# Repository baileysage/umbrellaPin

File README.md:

# umbrellaPin
Umbrella PCB for soldering classes ages ~8-14

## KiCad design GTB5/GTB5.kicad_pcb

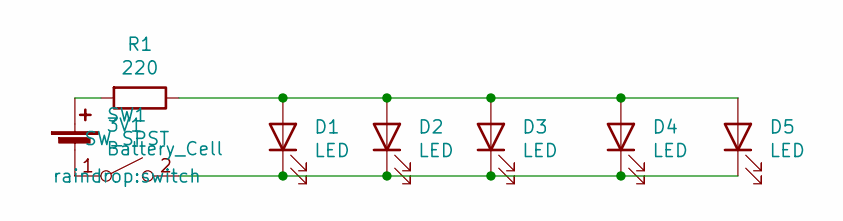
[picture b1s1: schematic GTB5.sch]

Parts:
3V1: Battery_Cell; BatteryHolder_BK_883
D1, D2, D3, D4, D5: LED; LED_D3.0mm_Clear
R1: 220; R_Axial_DIN0204_L3.6mm_D1.6mm_P7.62mm_Horizontal
SW1: SW_SPST; switch

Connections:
unnamed: 3V1.1 (+), R1.2
unnamed: 3V1.2 (-), SW1.1 (A)
unnamed: D1.1 (K), D2.1 (K), D3.1 (K), D4.1 (K), D5.1 (K), SW1.2 (B)
unnamed: D1.2 (A), D2.2 (A), D3.2 (A), D4.2 (A), D5.2 (A), R1.1

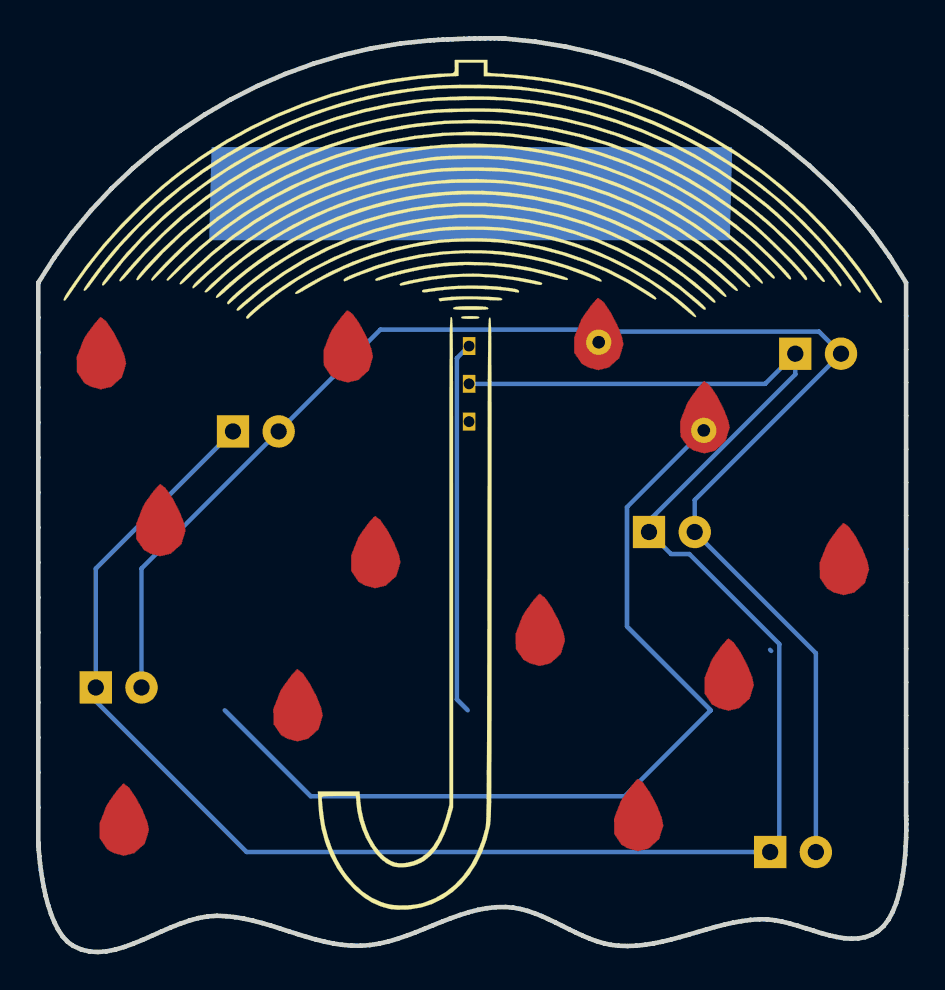
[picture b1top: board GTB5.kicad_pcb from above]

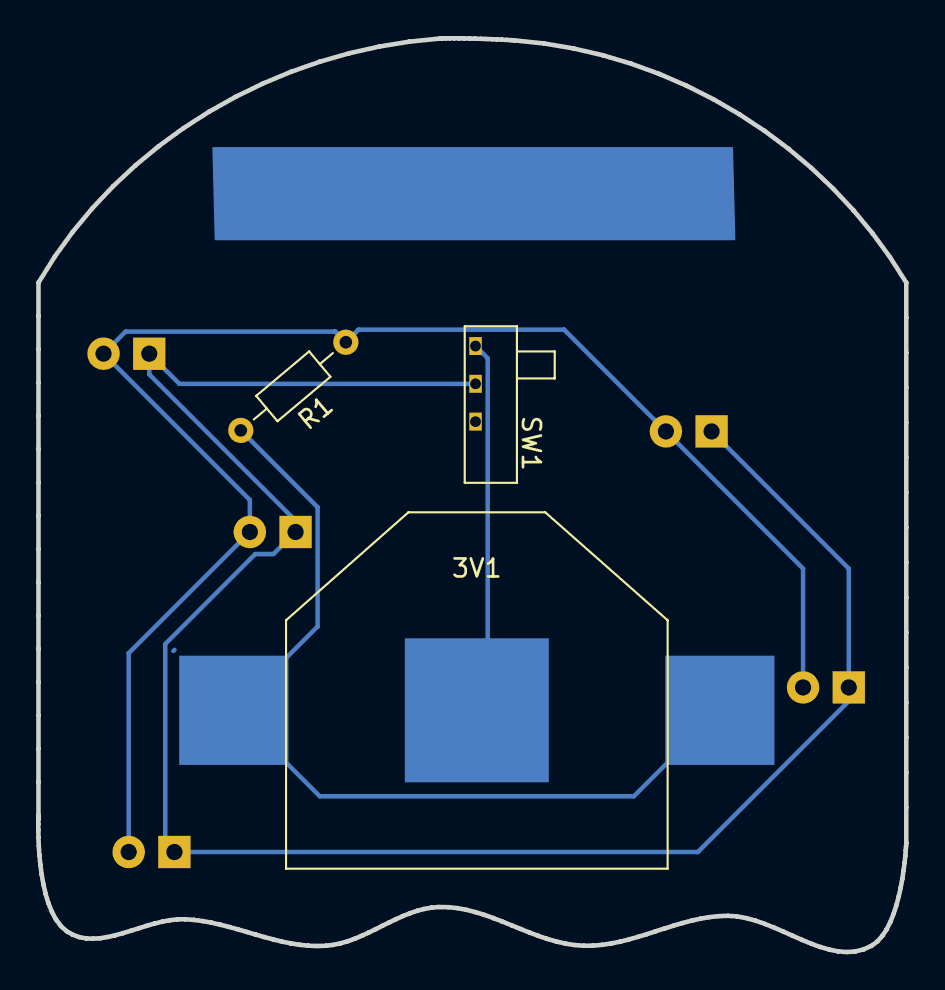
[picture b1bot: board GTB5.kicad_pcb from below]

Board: 2 copper layers, 48.2 x 50.8 mm, 21 parts (3 on the bottom side), 4 nets.

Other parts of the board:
Drop1, Drop2, Drop3, Drop4, Drop5, Drop6, Drop7, Drop8, Drop9, Drop10, Drop11, Drop12: raindrop
Umbrella: umbrella

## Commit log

2022-07-07 adding KiCAD files
2023-04-23 update to kicad 7
